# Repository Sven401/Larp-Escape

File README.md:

# Larp-Escape

ESP32-Steuerung des Reichstag-Spiels: Rollenkarten, Kristallmatrix, Audio, LEDs und ESP-NOW-Aktivierung.

**Entwicklungseinstieg · 20.10.2026:** Kanonische Basis ist
`plan/projektuebergabe-kuratierter-stand`, hier gegen `97a2584` geprüft.
Der [Maintainer-Stand](handoff/MAINTAINER.md) führt nächste Arbeit und Grenzen;
[Setup und Prüfwege](handoff/PROJEKT-SETUP.md) erklären die Arbeitsumgebung.
Die [technische Übergabe](handoff/README.md) erschließt datierte Belege und Archive.

| Arbeitsbereich | Vorhandene Grundlage | Einstieg und offene Fortsetzung |
| --- | --- | --- |
| **Larp Dev** · `companion/android/app/` | Baugruppenbedienung und Tests für LED, Wake, Matrix, Audio, NFC und ESP-NOW | [Android-Anleitung](companion/android/README.md); berührte Funktionen am passenden V2-Paar gezielt nachprüfen |
| **Larp GM** · `companion/android/gamemaster/` | Eigenständige App: Station vorbereiten, auswählen, automatisch anmelden und bestätigten Zustand lesen | [Stationspilot](docs/companion/spielleiter-stationspilot.md); Licht-/Spielaktionen und allgemeine Spielleitungsrechte bleiben offen |
| **Baugruppenfirmware** · `firmware/led/` | Gemeinsamer BLE-V2-Vertrag und getrennte Produkt-/Prüfvarianten; eigenständige Kamera-/Effektlabore | [Firmware-Anleitung](firmware/led/README.md), [Wire V2](docs/led/ble-wire-v2.md); gemeinsame Geräteabnahme und Spielanschluss bleiben offen |
| **Spiel- und Profilkern** · `src/`, `include/`, `lib/` | Bestehendes festes Spiel sowie konfigurierbarer Profilkern mit synthetischen Runtime-Proben | [Geräteausführung](docs/configuration/device-runtime.md), [Profilanwendung](docs/configuration/profile-application.md); reale profilabhängige Gerätebesitzer und Produktionsanschluss bleiben offen |

Die Produktquellen sind seit Stationspilot-Merge `7e19c95` unverändert;
die [Wartungsprüfung vom 20.10.2026](handoff/WARTUNG-PRUEFSTAND-2026-10-20.md)
belegt lokale Tests und Builds dieses Standes. Die historischen
[Baugruppenergebnisse](handoff/BAUGRUPPEN-NACHWEISE.md) und der begrenzte
GM-Gerätelauf bleiben erhalten; sie sind keine gemeinsame Gesamtspielabnahme.

**Verbindliches Zielbild:** [Dezentrale Veranstaltung (VA-01)](docs/veranstaltungsarchitektur.md)
mit autonomen Boxen, BLE je Station und unterbrechbarer Infrastruktur.
[D0 und Folgepakete](docs/veranstaltungsarchitektur-umsetzung.md) trennen die
integrierte Spezifikation von ihrer offenen Umsetzung. Für LED-Arbeit gelten
die [Projektgrenzen](docs/led/implementation-reference.md); Näheglut hat einen
[Laborstand und offenen Produktanschluss](docs/led/naeheglut-spielanschluss.md).

## Entwicklung ohne Hardware

PlatformIO Core **6.2.0**, Python **3.11** für B0; der vollständige Python-/Kameratestlauf benötigt **3.12**. Plattformen und Bibliotheken sind in `platformio.ini` festgelegt. Der Host verwendet Windows und C++11. Ein ESP32 wird für diese Schritte nicht benötigt:

```powershell
python scripts/check_architecture.py --self-test
python scripts/check_architecture.py
pio test -e host-regression
pio run -e az-delivery-devkit-v4 -e esp32-runtime-probe
python scripts/check_headers.py
python -m pip install clang-format==19.1.7
python scripts/check_format.py
```

Der [vollständige Prüfweg](docs/quality-checks.md) umfasst zusätzlich konfigurierte
Steuerung, echte Kryptografie, die GATTS-ABI-Probe und Android. Die CI prüft bei
Pull Requests den Zusammenführungsstand mit dem Zielbranch und bewahrt
commitbezogene Prüfprotokolle auch bei Fehlern. Hosttests und Firmware-Build
sind getrennte Nachweise; sie bestätigen weder Verdrahtung noch Timing am Gerät.

## Module

| Schicht | Ort | Aufgabe |
| --- | --- | --- |
| Domain | `include/GameDomain`, `src/GameDomain` | Rollen, Kristalle, Fortschritt und Resetregeln |
| Konfiguration | `include/GameConfiguration`, `src/GameConfiguration` | Begrenzte Profile, semantische Prüfung, JSON-Import/-Export |
| Ausführung | `include/GameExecution`, `src/GameExecution` | Konfigurierbarer Graph und profilabhängige Spielsitzung |
| Geräteplanung | `include/DeviceRuntime`, `src/DeviceRuntime` | Komponentenbesitz, korrelierte kopierte Aufträge und Antworten |
| Ports | `include/GamePorts` | Wertbasierte Schnittstellen für Geräte und Diagnose |
| Anwendung | `lib/GameState`, `lib/GameApplication` | Spielfluss und Reihenfolge der Dienste |
| Zustandsmaschine | `lib/Machine` | Zustandsbesitz, Guards, einmalige Eintrittsaktionen |
| Zeit-/Indexregeln | `include/GameRuntime` | Hostprüfbare Gerätepolitik ohne Treiber |
| Companion-Protokoll | `include/Companion`, `src/Companion` | Begrenzte Statusserialisierung ohne Netzwerkabhängigkeit |
| Adapter | übrige `lib`-Module | Arduino, FreeRTOS und konkrete Geräte |
| Einstieg | `src/main.cpp` | Aufbau, Start und Laufzeitdiagnose |

Die Spiellogik braucht weder Arduino noch Hardware-Stubs. Die alte Regression prüft zusätzlich die konkrete Farbpalettenzuordnung mit kleinen FastLED-Wertstubs; das ist ein Adaptervertrag.

## Laufzeit und Companion

- [ESP32 am USB ohne Zusatzhardware](docs/usb-probe.md)
- [NFC-Paketvertrag und gepinnte Bibliothekskorrektur](docs/nfc-packet-contract.md)
- [Komponentenplanung und FreeRTOS-Auftragskanal](docs/configuration/device-runtime.md)
- [Kontrollierte Profilübernahme und geänderte Einrichtung](docs/configuration/activation.md)
- [Aktives Profil und geschützter Entwurf](docs/configuration/profile-slots.md)
- [Dauerhafte Profile und Wiederanlauf](docs/configuration/profile-journal.md)
- [Gemeinsamer Einrichtungs-/Speicherablauf](docs/configuration/profile-application.md)
- [Profilabhängige Spielsitzung](docs/configuration/session.md)
- [Besitz, Tasks und Grenzen](docs/runtime.md)
- [Companion-Status v1](docs/companion/status-v1.md)
- [Statusschema](docs/companion/status-v1.schema.json)

Unter `companion/android/` liegen die getrennten Kotlin-/Compose-Apps Larp Dev
und Larp GM mit gemeinsamem `core:protocol`. [Apptrennung und Datenerhalt](docs/companion/android-app-trennung.md)
sowie der [lesende GM-Stationspilot](docs/companion/spielleiter-stationspilot.md)
sind implementiert. Allgemeiner Spielzugang, Spielsteuerung und veranstaltungsweite
Verteilung bleiben offen; der Baugruppen-HMAC-Zugang ersetzt keine GM-Rollen.

Die technische Übergabe in `handoff/` ist ohne Zugriff auf frühere interne
Projektwerkzeuge lesbar. Sie nennt die erhaltenen Commitstände, Prüfungen und
offenen Arbeiten.

## Qualitätsumfang

`check_architecture.py` prüft direkte Includes und Schichtrichtungen, nicht den vollständigen C++-Abhängigkeitsgraphen. Makro-Includes und unbekannte Projektincludes scheitern sichtbar. `--self-test` führt sieben isolierte Fixtures aus.

`check_headers.py` übersetzt jeden öffentlichen Header der reinen Schichten separat mit C++11, `-Wall -Wextra -Wpedantic -Werror`, ohne Hardware-Stubs. Der Hostcompiler wird nach den Hosttests von PlatformIO bereitgestellt.

`check_format.py` verwendet exakt clang-format **19.1.7** und `.clang-format`. Die explizite Baseline umfasst die reinen Schichten, die im Skript genannten überarbeiteten Adapter, beide Einstiegspunkte und die neuen Host-Suites. Alte Konfiguration, ArduinoClock, EspNowCommunicator und die frühere `test_regression` bleiben außerhalb der Formatbaseline. `--list` zeigt die konkreten Dateien, `--fix` formatiert ausschließlich diese geprüfte Liste. Den aktuellen Dateiumfang liefert `--list`; neue reine Schichten und der Profilkanal sind einbezogen.

Die Windows-CI ersetzt keine zusätzliche Prüfung von Include-Groß-/Kleinschreibung auf einem case-sensitiven System. Statische Analyse wurde lokal mit Cppcheck 2.1 für die reinen Implementierungen (`warning,performance,portability`) durchgeführt; clang-tidy und eine verpflichtende vollständige Analyse sind noch offen.

## Konfigurierbare Firmware und Companion

Der erste hardwarefreie Profilkern enthält Hardware, Rollen, Zustände, Übergangsbedingungen, Aktionen und Effekte. [Modell, Export und Grenzen](docs/configuration/profile-model.md), [Standardprofil](docs/configuration/standard-profile.json) und [strukturelles JSON-Schema](docs/configuration/profile-v1.schema.json). JSON-Import, Graphauswertung und eine profilabhängige Spielsitzung mit Rechnerbedienung sind implementiert. Komponentenplanung, Broker, statische FreeRTOS-Queues und kontrollierte Profilübernahme mit zwei privaten Profilspeichern sind implementiert und separat mit synthetischen Besitzern baubar. Zwei-Datensatz-Journal und synchronisierter Rechner-Dateispeicher sind implementiert; der ESP32-Speicheradapter ist an die separat gebaute FreeRTOS-Probe angeschlossen. Der gemeinsame Anwendungsablauf koordiniert Einrichtung, Speicherbestätigung und Spielleiterfreigabe in Rechnerwerkzeug und Probe. Für diesen Profilpfad bleiben reale profilabhängige Treiber, Produktionsanschluss, Geräte-/Stromausfallabnahme und die Anbindung an die Android-Apps offen.

Konfigurierbare Graphausführung und Rechner-Vorschau: [Laufzeitvertrag](docs/configuration/execution.md).

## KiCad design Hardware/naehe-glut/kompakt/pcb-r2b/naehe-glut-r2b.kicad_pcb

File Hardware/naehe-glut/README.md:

# Nähe Glut R1: Platine, Gehäuse und Beschaffung

**Historischer R1-Stand, keine aktuelle Bestellbasis:** Der Nutzer verlangt
seit31.10.2026 kleinsten Gesamtformfaktor, ESP-Boards höchstens25×20mm,
vier Stunden Akkulaufzeit als Auslegungsziel und vollständig bestückte Platinen.
Die [Kompaktplanung](kompakt/PLANUNG.md) ersetzt die bisherige Größen-/Teilewahl.
R1 bleibt für Bestellung und Fertigung gesperrt. Eine spätere Autorisierung
der neuen Kompaktvariante hebt diesen R1-Bestellstopp nicht auf.

Stand: **31. Oktober 2026**. Prototyprevision für zwei ESP32-S3-Stationen.
Digitale Fertigungsunterlagen sind erstellt; der abschließende Freigabestand
und konkrete Prüfgrenzen stehen im [unabhängigen Review](REVIEW.md).
Es wurde noch nichts bestellt, gedruckt, bestückt oder auf Geräte geladen.

## Benutzen

- [PCB-Fertigungspaket als ZIP](pcb/exports/naehe-glut-r1-fertigung.zip)
  und [Druckpaket als ZIP](fertigung/NG-R1-Druckpaket.zip).
- [Bestellliste für beide Geräte](BESTELLUNG.md): Boards, Ringe, Akkus,
  Drucker, Filament, Kabel und Montagebedarf.
- [PCB-Bauteile](pcb/BOM.md) und [Fertigung/elektrische Montage](pcb/FERTIGUNG.md).
- [Gehäusemontage](mechanik/MONTAGE.md) und [Druckprojekte/Prüfweg](mechanik/DRUCK.md).
- Native KiCad-Dateien unter `pcb/`; FCStd, STEP und STL unter `mechanik/`;
  sechs vorbereitete A1-mini-Projekte unter `mechanik/print/`.

## Festgelegter Aufbau

ESP32-S3-DevKitC-1-N16R8 von Espressif, Adafruit-1586-Ring mit **24 Pixeln**,
Voltaic-V50-Akku und zweilagige Carrierplatine, 85×80 mm. GPIO15 führt
LED-Daten, GPIO16 gibt die 5-V-Pufferstufe frei. Der Carrier versorgt keine
ESP-5V-/3V3-Pins; zwei USB-A-Kabel vom Akku speisen getrennte Pluspfade bei
gewollt gemeinsamer Masse. Laden erfolgt mit entnommenem Akku.

Beschaffungsänderung vom 31.10.2026 auf Basis `e9e2afe`: Das lieferbare
Original-N16R8 ersetzt N8R8 mit denselben Carrieranschlüssen. Der Schaltplan
behält die ursprüngliche N8R8-Bezeichnung; mechanische und elektrische
Carrierdateien bleiben unverändert. Die Firmware braucht 16 MB Quad-Flash
und weiterhin 8 MB Octal-PSRAM; eine Geräteprüfung steht aus.

Das PETG-Gehäuse misst 168×148×90 mm ohne Schraubenköpfe. Boden, Träger,
Deckel, Ringhalter und Diffusor sind getrennt druckbar; ein Coupon prüft
vorab Schrauben-/Mutternpassung. Drucker: Bambu Lab A1 mini, 0,4-mm-Düse,
ohne AMS. Vier Nylonbefestiger halten die PCB im Antennenbereich. Schwarze
Teile verwenden nun **Bambu PETG Basic 30105**, der Diffusor weiter PETG
Translucent Clear. Alle sechs Druckprojekte sind neu berechnet; etwa 11,7 Stunden
Maschinenzeit je Station. Beschaffungsquellen und Trocknung stehen in der Bestellliste.

Die Auslegung gilt für trockenen, vor Regen geschützten Einsatz. Eine konkrete
Mindestlaufzeit wurde nicht vorgegeben; die Bestellliste enthält gekennzeichnete
Laufzeitrechnungen. Keine IP-, Wärme- oder Funkfreigabe wird aus CAD/Slicer
abgeleitet. Ein ausgeschalteter ESP löscht gespeicherte Pixelfarben nicht;
für Service beide Versorgungszweige trennen.

## Auftrag, Zuständigkeit und Termin

Quelle: Nutzerauftrag in Codex-Sitzung `01a192e5-6a3d-7ce2-a9e1-bfacd9a97e3b`,
31.10.2026, Basiscommit `63477d08e160d1b1f81b37bbd16593c1a2087624`:
bestellbare PCB und druckbares Gehäuse; Komponentenwahl, Akkukonzept und
Druckerauswahl ausdrücklich delegiert.

Koordination/Maintainer und Beschaffung: `/root`; Elektronik:
`/root/hardware_developer`; Mechanik: `/root/enclosure_developer`;
unabhängige Gegenprüfung Gerätevertrag/Qualität: `/root/hardware_review`.
Beschaffungsnachtrag: `/root` verantwortlich, `/root/filament_supply` setzt
Materialprofile um, `/root/supply_review` prüft unabhängig gegen.
Eigene Umsetzung gilt nicht als unabhängiger Review.

**Zwei funktionierende Exemplare bis Dezember 2026 bleiben das Lieferziel.**
Eine eigene PCB darf diesen Termin nicht gefährden. Die
[kanonische Hardwareplanung](../HARDWAREPLANUNG.md) behält Vorrang; bei
Fertigungsrisiko ist parallel ein Aufbau mit vorhandenen Boards/Modulen
vorzusehen. Das genaue Dezemberdatum ist weiterhin offen.

Diese Dateien liefern die Hardwareentwicklung. Firmwareportierung auf S3/R1,
schwarzer Startframe mit 24 Pixeln, Effekt/Funk zwischen beiden Geräten,
Probemontage, Last-/Wärmeprüfung und Dauerlauf bleiben gesonderte Arbeit.
Die alte ESP32-Box und ihr 23-Pixel-Aufbau werden durch R1 nicht umgebaut.

## Werkzeuge und Nachweise

| Bereich | Werkzeug / Beleg | Aussage |
| --- | --- | --- |
| Elektronik | KiCad 10.0.8; `pcb/pruefung/` | ERC, DRC, Netzlisten-/Layoutabgleich und CAM-Prüfung gemäß Review |
| Geometrie | FreeCAD 1.0.2; `mechanik/geometry-report.json` | Gültige Körper, STEP-Rückimport, geschlossene STL-Netze, Kollisionen und Bezug auf den echten PCB-STEP |
| Druck | Bambu Studio 2.8.2.61; `mechanik/slice-report.json` | Alle sechs Teile erfolgreich berechnet; Datei-Hashes, Material und Zeitabschätzungen |
| Gegenprüfung | `REVIEW.md` | Unabhängige konkrete Befunde, Freigabeumfang und offene physische Nachweise |

Generatoren liegen unter `tools/`. Montage- und Druckanleitungen nennen die
reproduzierbaren Aufrufe. Lokale Werkzeugdownloads, Probeläufe und Sicherungen
unter `.tmp/` sind keine Lieferdateien. PCB-Änderungen erfordern neuen Export
und Geometrieabgleich; Änderungen an Druckteilen erfordern neue Slicerprojekte.

„Bestellbar“ bedeutet geprüftes Prototyp-Fertigungspaket mit eindeutiger
Stückliste, keine gesicherte Lagerverfügbarkeit und keinen ausgelösten Kauf.
„Druckbar“ bedeutet digital geprüfte Druckdateien, keine bestandene physische
Passprobe oder Produktabnahme.

## Abgrenzung bestehender Vorarbeiten

[Issue #112](https://github.com/Sven401/Larp-Escape/issues/112) und
[PR #113](https://github.com/Sven401/Larp-Escape/pull/113) führen das
Vollboxkonzept PCB-K0. DFPlayer, MCP und weitere Vollboxfunktionen werden
daraus nicht als Bauumfang dieser Nähe-Glut-Variante übernommen.
Historische Schaltplanquellen bleiben im [Quelleninventar](../QUELLENINVENTAR.md).

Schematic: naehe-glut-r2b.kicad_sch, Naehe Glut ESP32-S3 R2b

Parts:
C1, C2: 10uF 10V X5R; C_0805_2012Metric; MPN GRM21BR61A106KE19L
C3, C4, C6, C17, C18: 22uF 16V X6S; C_0805_2012Metric; MPN GRM21BC81C226ME44L
C5, C7, C20: 10uF 25V X5R; C_0603_1608Metric; MPN TMK107BBJ106MA-T
C8, C9, C11, C19: 100nF 16V X7R; C_0402_1005Metric; MPN GRM155R71C104KA88D
C10, C12: 1uF 10V X5R; C_0402_1005Metric; MPN GRM155R61A105KE15D
C13: 22nF 50V X7R; C_0402_1005Metric; MPN GRM155R71H223KA12D
C14: 22uF 10V X5R; C_0805_2012Metric; MPN GRM21BR61A226ME44L
C16: 470uF 6.3V polymer10mOhm; CP_EIA-7343-43_Kemet-X; MPN T530X477M006ATE010
C21: 1uF 10V X5R startup delay; C_0603_1608Metric; MPN GRM188R61A105KA61D
C22: 220pF 50V C0G feedforward; C_0402_1005Metric; MPN GRM1555C1H221JA01D
C23, C24, C25: 100n; C_0603_1608Metric; MPN GRM188R71C104KA01D
C26, C27: 10n; C_0603_1608Metric; MPN GRM188R71H103KA01D
C28: 100n 16V X7R / input not stability-critical; C_0603_1608Metric; MPN GRM188R71C104KA01D
C29, C30: 4.7u 16V X7R / two parallel for bias reserve; C_0805_2012Metric; MPN GRM21BR71C475KE51L
C31: 100n inverter bypass; C_0603_1608Metric; MPN GRM188R71C104KA01D
D1, D2, D3, D4, D5: rail-free ESD array; Texas_DRT-3; MPN TPD2EUSB30DRTR
F1: 2A fast fuse; Fuse_0603_1608Metric; MPN 0467002.NRHF
J1: BAT JST PH2 vertical; JST_PH_B2B-PH-SM4-TB_1x02-1MP_P2.00mm_Vertical; MPN B2B-PH-SM4-TB(LF)(SN)
J2: LED wire pads; LED_3WirePads; MPN PCB integral solder pads
J3: External EG1218 EN switch; Switch_2WirePads; MPN PCB integral solder pads
J4: USB-C DATA ONLY / external target supply; USB_C_Receptacle_GCT_USB4105-xx-A_16P_TopMnt_Horizontal; MPN USB4105-GF-A
J5: GPIO JTAG / VTref reference only; FTSH105_007_K; MPN FTSH-105-01-L-DV-007-K
JP1: OPEN USB / CLOSED GPIO after authorized eFuse; PinHeader_1x02_P2.54mm_Vertical; MPN TSW-102-07-G-S
L1: 1uH; L_Coilcraft_XxL4030; MPN XEL4030-102MEC
L2: 1.5uH; L_Coilcraft_XAL4020-XXX; MPN XFL4020-152MEC
Q1: MMBT3904 NPN OE pull-down; SOT-323_SC-70; MPN MMBT3904WT1G
R1: 33.2k; R_0402_1005Metric; MPN 0402WGF3322TCE
R2, R7: 100k; R_0402_1005Metric; MPN RT0402BRD07100KL
R3: 12.1k; R_0402_1005Metric; MPN RT0402BRD0712K1L
R4, R6: 750k; R_0402_1005Metric; MPN MCS0402MD7503BE000
R5: 22k; R_0402_1005Metric; MPN RC0402FR-0722KL
R8, R9, R10, R11, R24, R26: 10k; R_0402_1005Metric; MPN RC0402FR-0710KL
R12, R14, R16, R19: 100k; R_0402_1005Metric; MPN RC0402FR-07100KL
R13: 100; R_0402_1005Metric; MPN RC0402FR-07100RL
R15: 330; R_0402_1005Metric; MPN RC0402FR-07330RL
R17: 470 ohm 0.1W; R_0603_1608Metric; MPN RC0603FR-07470RL
R18: 680; R_0402_1005Metric; MPN RC0402FR-07680RL
R22: 470k; R_0402_1005Metric; MPN MCS0402MD4703BE000
R23: 150k; R_0402_1005Metric; MPN RT0402BRD07150KL
R25: 6.8k; R_0402_1005Metric; MPN RC0402FR-076K8L
R27: 1k; R_0402_1005Metric; MPN RC0402FR-071KL
R28, R29: 5K1; R_0402_1005Metric; MPN RC0402FR-075K1L
R30, R31: 22R; R_0402_1005Metric; MPN RC0402FR-0722RL
R32, R33, R34, R35, R46: 10K; R_0402_1005Metric; MPN RC0402FR-0710KL
R36, R37, R38, R39: 33R; R_0402_1005Metric; MPN RC0402FR-0733RL
R40: 200K; R_0402_1005Metric; MPN RT0402BRD07200KL
R41: 75K; R_0402_1005Metric; MPN RT0402BRD0775KL
R42, R45: 47K; R_0402_1005Metric; MPN RC0402FR-0747KL
R47: 169K; R_0402_1005Metric; MPN RT0402BRD07169KL
R48: 100K; R_0402_1005Metric; MPN RT0402BRD07100KL
SW1: BOOT; SW_Push_1P1T_NO_CK_KMR2; MPN KMR221NGLFS
SW2: RESET; SW_Push_1P1T_NO_CK_KMR2; MPN KMR221NGLFS
TP1: UART0_TX_GPIO43; TestPad_1mm; MPN PCB integral test pad
TP2: UART0_RX_GPIO44; TestPad_1mm; MPN PCB integral test pad
TP3: ROM_BOOT0; TestPad_1mm; MPN PCB integral test pad
TP4: RESET_EN; TestPad_1mm; MPN PCB integral test pad
TP5: GND; TestPad_1mm; MPN PCB integral test pad
TP6: SENSE_ONLY_NO_POWER_IN; TestPad_1mm; MPN PCB integral test pad
U1: ESP32-S3-MINI-1-N4R2; ESP32-S2-MINI-1; MPN ESP32-S3-MINI-1-N4R2
U2: 5.1V LED boost; SOT-563; MPN TPS61023DRLR
U3: 3V3 independent buck-boost; TI_RNM0015A; MPN TPS63070RNMR
U4: UVLO with hysteresis; SOT-23-6; MPN TPS3700DDCR
U5: LED input current limiter latch-off; SOT-23-6; MPN TPS2553DBVR-1
U6: LED translating data buffer; SOT-353_SC-70-5; MPN SN74LV1T125DCKR
U7: LED load switch; SOT-23-6; MPN TPS22918DBVR
U8: USB hardware disconnect; Texas_UQFN-10_1.5x2mm_P0.5mm; MPN TS3USB221ARSER
U9, U10: USB attach supervisor; TI_DSE0006A; MPN TPS389001DSER
U11: USB interface ONLY / no target power; SOT-23-5; MPN TPS70933DBVR
U12: USB ready Schmitt inverter; SOT-353_SC-70-5; MPN SN74LVC1G14DCKR

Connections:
/+3V3: C6.1, C7.1, C8.1, C17.1, C18.1, D4.2 (IO2), J5.1, R8.1, R9.1, R11.1, R22.1, R32.1, R33.1, R34.1, R47.1, TP6.1, U1.3 (3V3), U3.7 (VOUT), U3.8 (VOUT)
/+5V: C3.1, C4.1, C12.1, C22.1, R6.1, U2.6 (VOUT), U7.1 (VIN)
/BAT_FUSED: C1.1, C5.1, C9.1, C20.1, F1.2, R2.1, R5.1, R26.1, U3.12 (VIN), U3.13 (VIN), U4.5 (VDD), U5.1 (IN)
/BAT_LIMITED: C2.1, L1.1, U2.3 (VIN), U5.6 (OUT)
/BAT_RAW: F1.1, J1.1
/BOOST_FB: C22.2, R6.2, R7.1, U2.1 (FB)
/BOOST_SW: L1.2, U2.5 (SW)
/BOOT0: R9.2, SW1.1, TP3.1, U1.4 (IO0)
/CHIP_EN: D4.1 (IO1), J5.10, R8.2, R25.1, SW2.1, TP4.1, U1.45 (EN), U3.2 (PG)
/FAULT_N: R11.2, U1.15 (IO11), U5.4 (FAULT)
/GND: C1.2, C2.2, C3.2, C4.2, C5.2, C6.2, C7.2, C8.2, C9.2, C10.2, C11.2, C12.2, C13.2, C14.2, C16.2, C17.2, C18.2, C19.2, C20.2, C21.2, C23.2, C24.2, C25.2, C26.2, C27.2, C28.2, C29.2, C30.2, C31.2, D1.3 (GND), D2.3 (GND), D3.3 (GND), D4.3 (GND), D5.3 (GND), J1.2, J2.2, J3.2, J4.A1, J4.A12, J4.B1, J4.B12, J4.SH, J5.3, J5.5, JP1.2, Q1.2 (E), R1.2, R3.2, R7.2, R10.2, R12.2, R14.2, R16.2, R19.2, R23.2, R28.2, R29.2, R35.2, R41.2, R46.2, R48.2, SW1.2, SW2.2, TP5.1, U1.1 (GND), U1.2 (GND), U1.42 (GND), U1.43 (GND), U1.46 (GND), U1.47 (GND), U1.48 (GND), U1.49 (GND), U1.50 (GND), U1.51 (GND), U1.52 (GND), U1.53 (GND), U1.54 (GND), U1.55 (GND), U1.56 (GND), U1.57 (GND), U1.58 (GND), U1.59 (GND), U1.60 (GND), U1.61 (GND), U1.62 (GND), U1.63 (GND), U1.64 (GND), U1.65 (GND), U2.4 (GND), U3.4 (GND), U3.10 (PGND), U3.15 (VSEL), U4.2 (GND), U4.4 (INB-), U5.2 (GND), U6.3 (GND), U7.2 (GND), U8.5 (GND), U8.9 (S), U9.2 (GND), U10.2 (GND), U11.2 (GND), U12.3 (GND)
/GPIO8_DATA: R13.1, U1.12 (IO8)
/GPIO9_OE: R18.1, U1.13 (IO9)
/GPIO10_LED_EN: R12.1, U1.14 (IO10), U2.2 (EN), U5.3 (EN), U7.3 (ON)
/GPIO46_STRAP: R10.1, U1.44 (IO46)
/ILIM: R1.1, U5.5 (ILIM)
/JTAG_SEL: JP1.1, R32.2, U1.7 (IO3)
/JTAG_TCK: R35.1, R36.2, U1.35 (IO39)
/JTAG_TCK_PORT: D2.2 (IO2), J5.4, R36.1
/JTAG_TDI: R34.2, R38.2, U1.37 (IO41)
/JTAG_TDI_PORT: D3.2 (IO2), J5.8, R38.1
/JTAG_TDO: R39.1, U1.36 (IO40)
/JTAG_TDO_PORT: D3.1 (IO1), J5.6, R39.2
/JTAG_TMS: R33.2, R37.2, U1.38 (IO42)
/JTAG_TMS_PORT: D2.1 (IO1), J5.2, R37.1
/LED5V: C11.1, C14.1, C16.1, J2.1, R17.1, R27.1, U6.5 (VCC), U7.6 (VOUT)
/LED_A: R13.2, R14.1, U6.2 (A)
/LED_CT: C13.1, U7.4 (CT)
/LED_DATA: J2.3, R15.2, R16.1
/LED_OE_N: Q1.3 (C), R17.2, U6.1 (OE_N)
/LED_QOD: R27.2, U7.5 (QOD)
/LED_Y: R15.1, U6.4 (Y)
/MCU_FB: R22.2, R23.1, U3.5 (FB)
/MCU_L1: L2.1, U3.11 (L1)
/MCU_L2: L2.2, U3.9 (L2)
/MCU_PS: R26.2, U3.1 (PS_SYNC)
/MCU_REG_EN: C21.1, R24.2, U3.14 (EN)
/MCU_VAUX: C19.1, U3.3 (VAUX)
/OE_GATE: Q1.1 (B), R18.2, R19.1
/RC_EN: C10.1, R25.2
/SYS_EN: J3.1, R4.1, R5.2, R24.1, U4.1 (OUTA)
/UART_RX: TP2.1, U1.40 (RXD0)
/UART_TX: TP1.1, U1.39 (TXD0)
/USB_CC1: D5.1 (IO1), J4.A5, R28.1
/USB_CC2: D5.2 (IO2), J4.B5, R29.1
/USB_DM_HOST: D1.2 (IO2), J4.A7, J4.B7, U8.7 (D-)
/USB_DM_ISO: R30.2, U8.2 (1D-)
/USB_DM_MCU: R30.1, U1.23 (USB_D-)
/USB_DP_HOST: D1.1 (IO1), J4.A6, J4.B6, U8.8 (D+)
/USB_DP_ISO: R31.2, U8.1 (1D+)
/USB_DP_MCU: R31.1, U1.24 (USB_D+)
/USB_IF_3V3: C23.1, C24.1, C25.1, C29.1, C30.1, C31.1, R42.1, R45.1, R46.1, U8.10 (VCC), U9.3 (MR_N), U9.4 (VDD), U10.3 (MR_N), U10.4 (VDD), U11.5 (OUT), U12.5 (VCC)
/USB_OE_N: R45.2, U8.6 (OE_N), U12.4 (Y)
/USB_READY: R42.2, U9.6 (RESET_N), U10.6 (RESET_N), U12.2 (A)
/USB_TARGET_CT: C26.1, U9.5 (CT)
/USB_TARGET_SENSE: R47.2, R48.1, U9.1 (SENSE)
/USB_VBUS: C28.1, J4.A4, J4.A9, J4.B4, J4.B9, R40.1, U11.1 (IN)
/USB_VBUS_CT: C27.1, U10.5 (CT)
/USB_VBUS_SENSE: R40.2, R41.1, U10.1 (SENSE)
/UV_SENSE: R2.2, R3.1, R4.2, U4.3 (INA+)

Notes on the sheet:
NAEHE GLUT R2b | ELECTRICAL DRAFT - NOT RELEASED FOR MANUFACTURING
Independent MCU buck-boost; current-limited LED boost; UVLO; USB data service, external target supply; no charger.
Battery pack/charger qualification and PWM transient survival remain mandatory order gates.

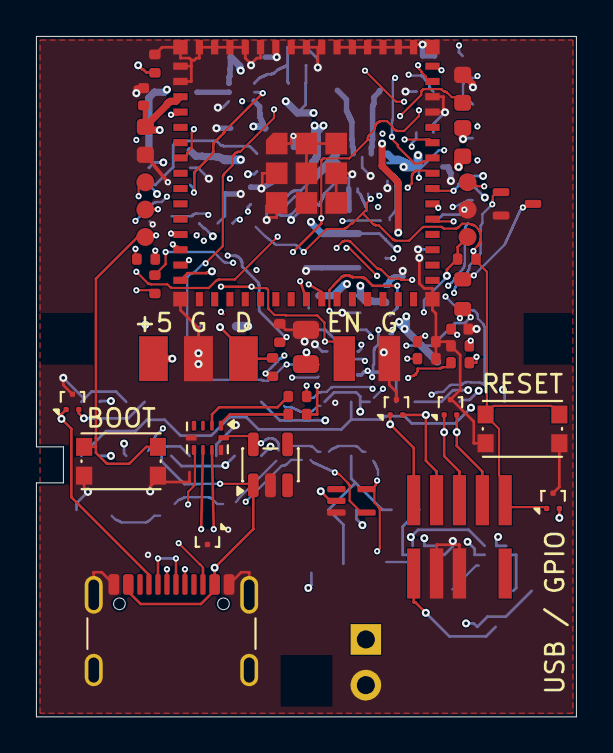
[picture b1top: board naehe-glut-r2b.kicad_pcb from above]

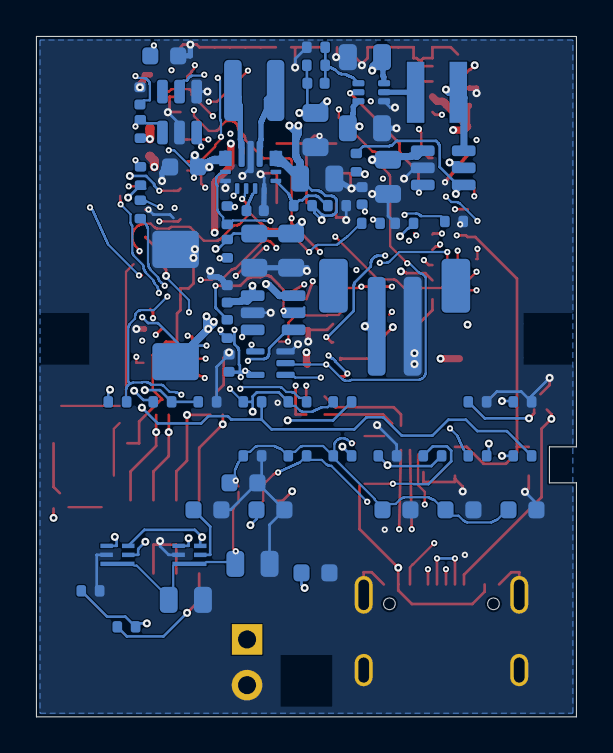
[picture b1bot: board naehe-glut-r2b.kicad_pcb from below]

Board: 6 copper layers, 30.0 x 37.8 mm, 109 parts (67 on the bottom side), 60 nets.

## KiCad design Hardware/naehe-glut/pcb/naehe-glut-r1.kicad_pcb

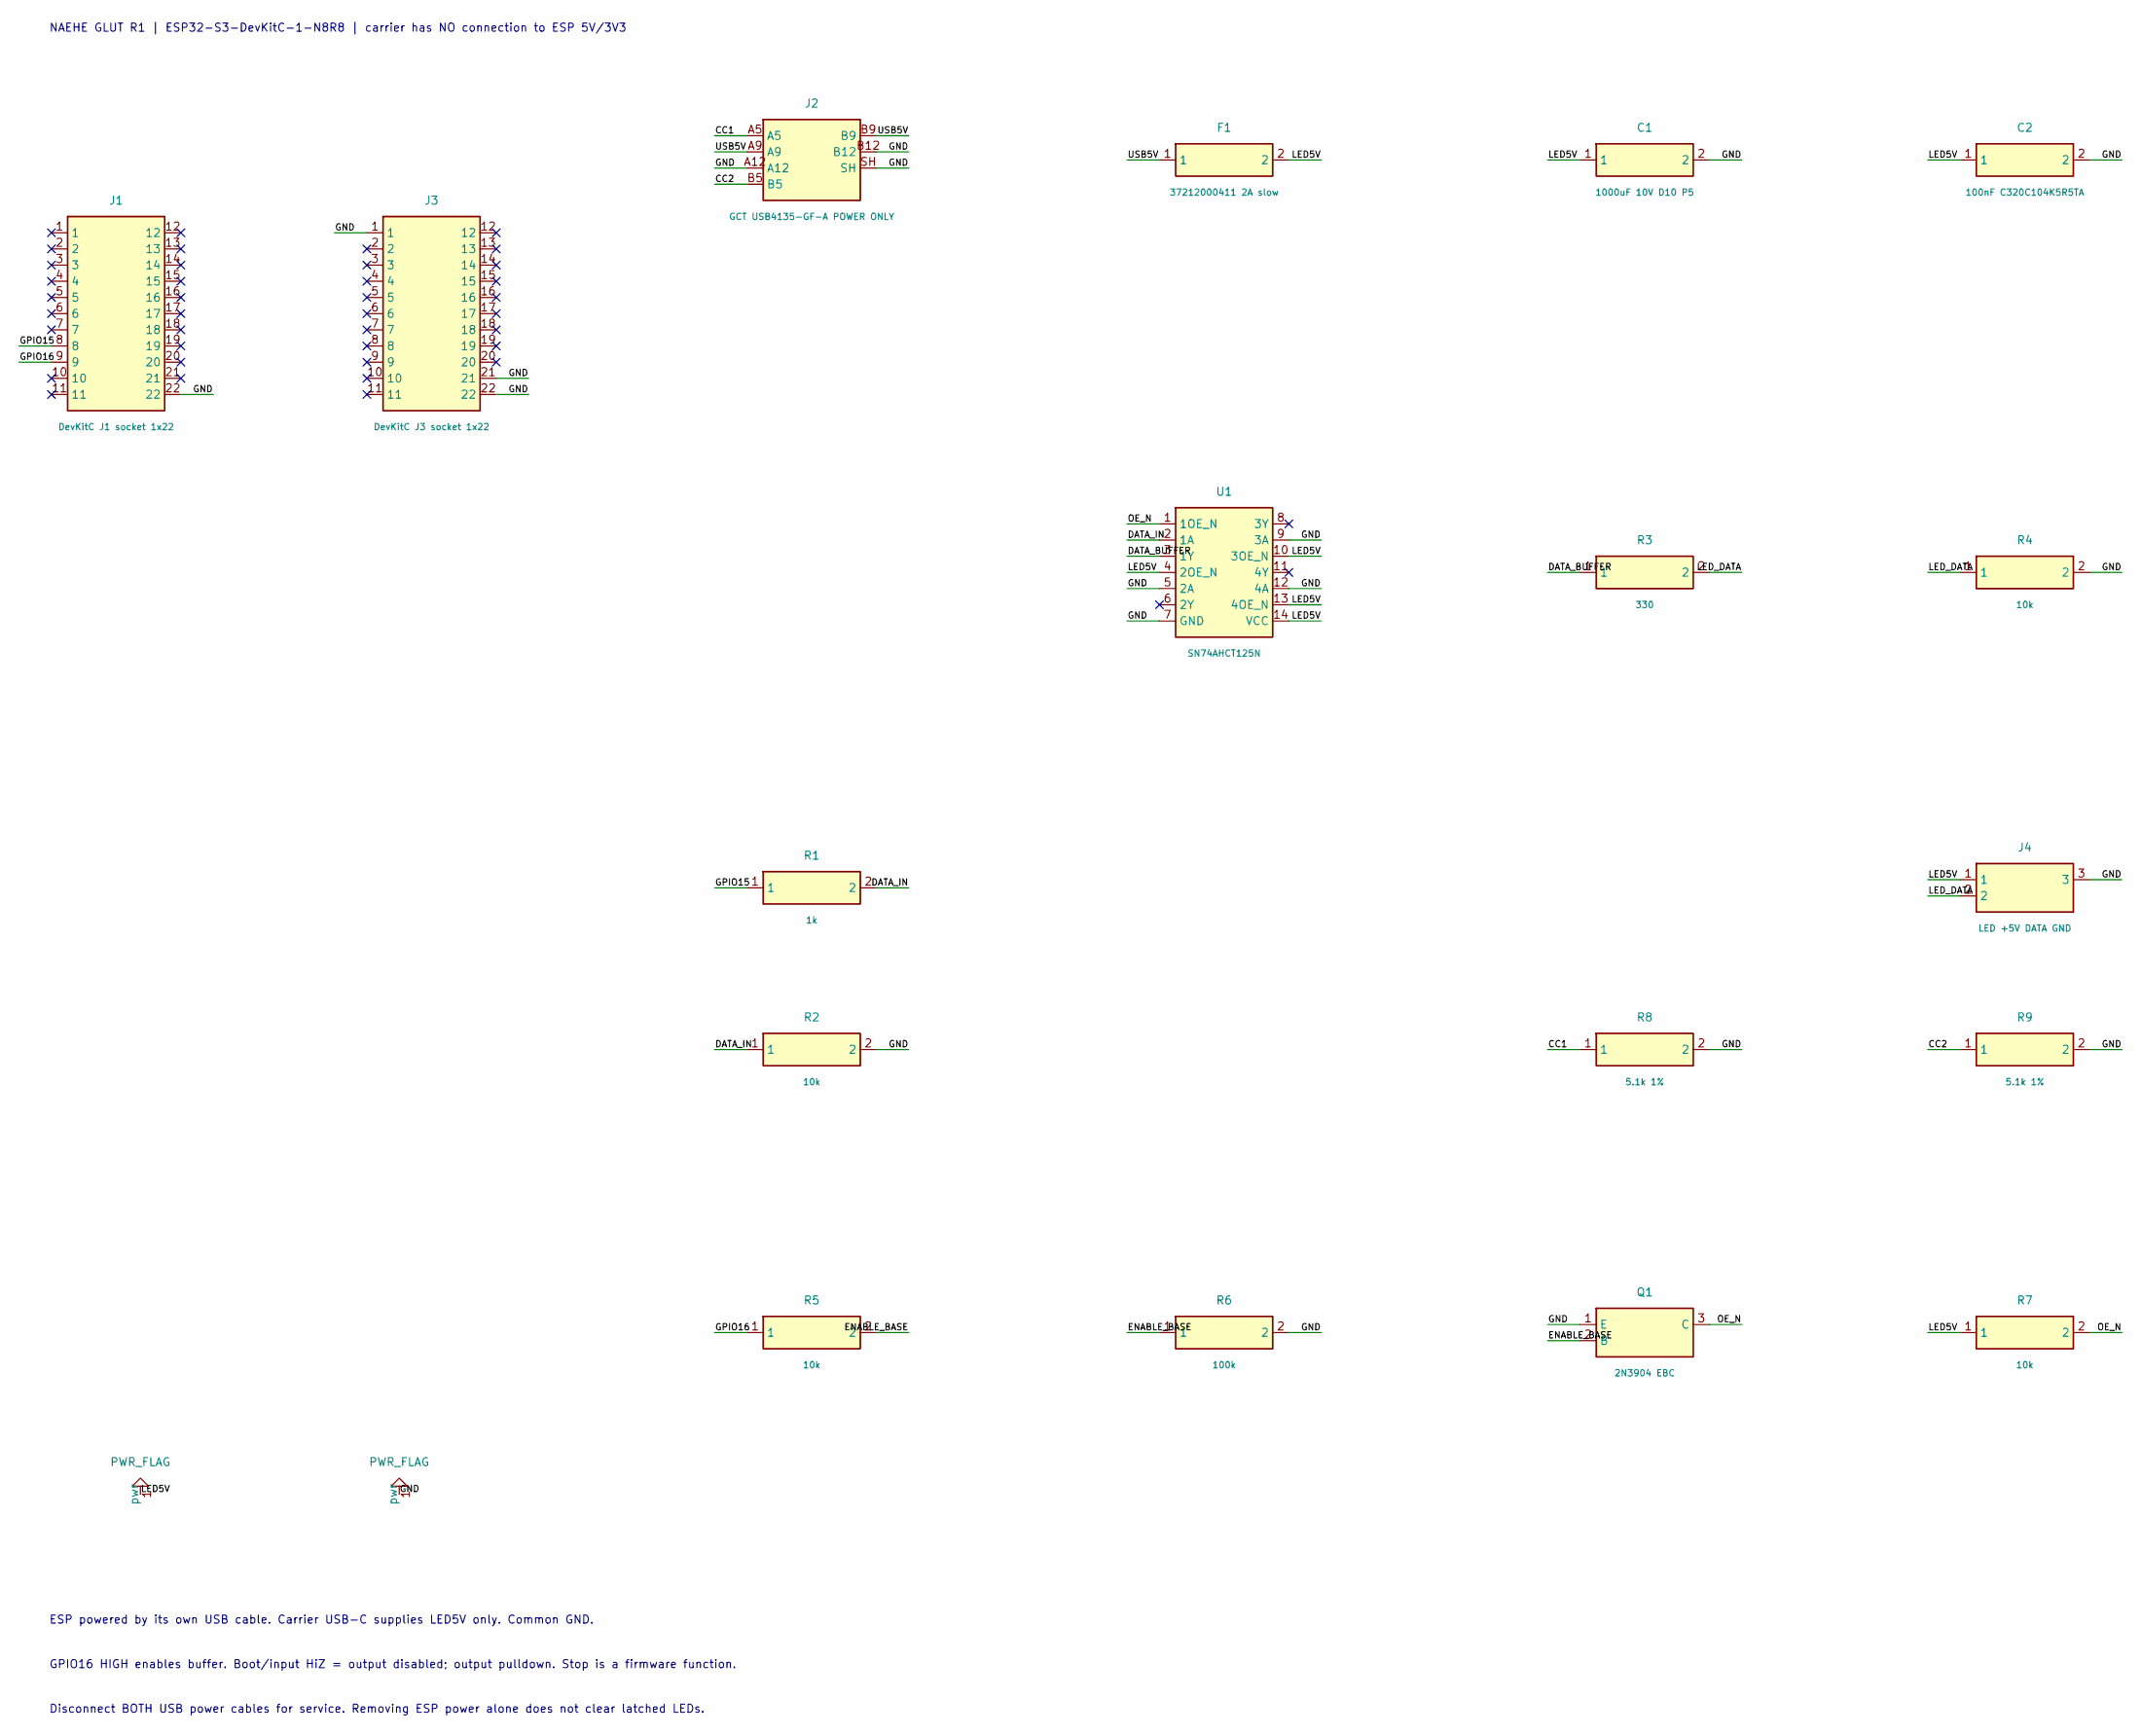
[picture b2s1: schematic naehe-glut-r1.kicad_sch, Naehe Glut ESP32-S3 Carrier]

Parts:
C1: 1000uF 10V D10 P5; CP_Radial_D10.0mm_P5.00mm
C2: 100nF C320C104K5R5TA; C_Kemet_C320_P2.54mm
F1: 37212000411 2A slow; Fuse_Littelfuse_372_D8.50mm
J1: DevKitC J1 socket 1x22; PinSocket_1x22_P2.54mm_Vertical
J2: GCT USB4135-GF-A POWER ONLY; USB_C_Receptacle_GCT_USB4135-GF-A_6P_TopMnt_Horizontal
J3: DevKitC J3 socket 1x22; PinSocket_1x22_P2.54mm_Vertical
J4: LED +5V DATA GND; TerminalBlock_Phoenix_MKDS-1,5-3-5.08_1x03_P5.08mm_Horizont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
Q1: 2N3904 EBC; TO-92_Inline_Wide
R1: 1k; R_Axial_DIN0207_L6.3mm_D2.5mm_P10.16mm_Horizontal
R2, R4, R5, R7: 10k; R_Axial_DIN0207_L6.3mm_D2.5mm_P10.16mm_Horizontal
R3: 330; R_Axial_DIN0207_L6.3mm_D2.5mm_P10.16mm_Horizontal
R6: 100k; R_Axial_DIN0207_L6.3mm_D2.5mm_P10.16mm_Horizontal
R8, R9: 5.1k 1%; R_Axial_DIN0207_L6.3mm_D2.5mm_P10.16mm_Horizontal
U1: SN74AHCT125N; DIP-14_W7.62mm

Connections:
/CC1: J2.A5, R8.1
/CC2: J2.B5, R9.1
/DATA_BUFFER: R3.1, U1.3 (1Y)
/DATA_IN: R1.2, R2.1, U1.2 (1A)
/ENABLE_BASE: Q1.2 (B), R5.2, R6.1
/GND: C1.2, C2.2, J1.22, J2.A12, J2.B12, J2.SH, J3.1, J3.21, J3.22, J4.3, Q1.1 (E), R2.2, R4.2, R6.2, R8.2, R9.2, U1.5 (2A), U1.7 (GND), U1.9 (3A), U1.12 (4A)
/GPIO15: J1.8, R1.1
/GPIO16: J1.9, R5.1
/LED5V: C1.1, C2.1, F1.2, J4.1, R7.1, U1.4 (2OE_N), U1.10 (3OE_N), U1.13 (4OE_N), U1.14 (VCC)
/LED_DATA: J4.2, R3.2, R4.1
/OE_N: Q1.3 (C), R7.2, U1.1 (1OE_N)
/USB5V: F1.1, J2.A9, J2.B9

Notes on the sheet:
NAEHE GLUT R1 | ESP32-S3-DevKitC-1-N8R8 | carrier has NO connection to ESP 5V/3V3
ESP powered by its own USB cable. Carrier USB-C supplies LED5V only. Common GND.
GPIO16 HIGH enables buffer. Boot/input HiZ = output disabled; output pulldown. Stop is a firmware function.
Disconnect BOTH USB power cables for service. Removing ESP power alone does not clear latched LEDs.

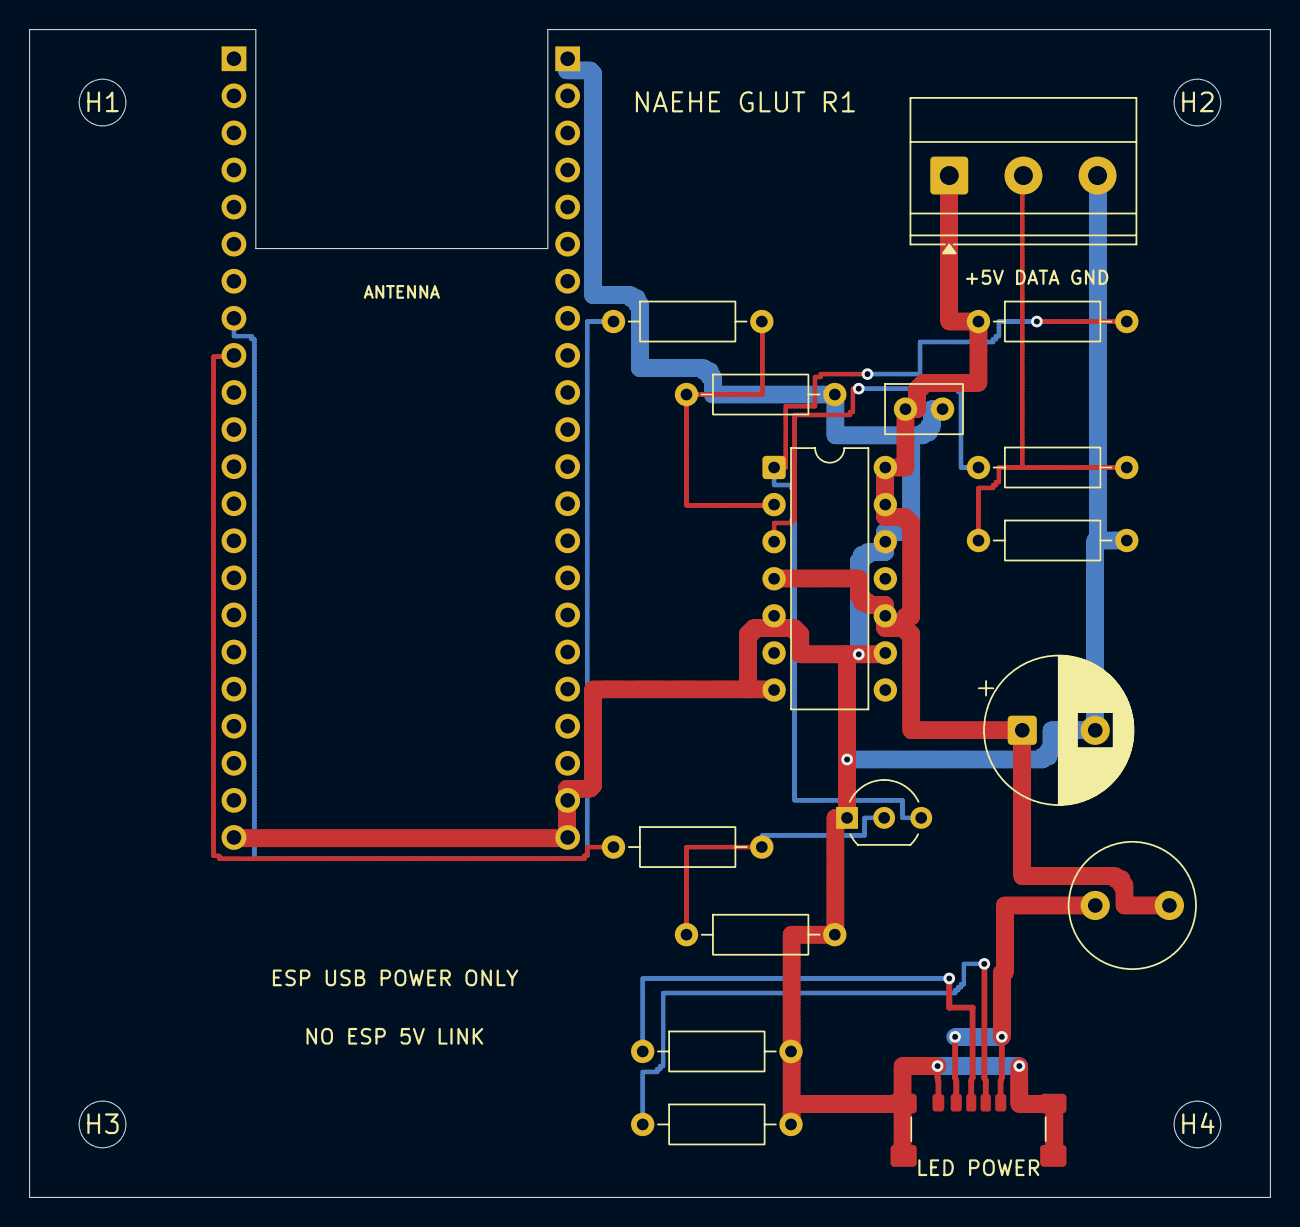
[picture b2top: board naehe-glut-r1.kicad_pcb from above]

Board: 2 copper layers, 85.0 x 80.0 mm, 22 parts (0 on the bottom side), 12 nets.

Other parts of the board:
H1, H2, H3, H4: M3 NPTH

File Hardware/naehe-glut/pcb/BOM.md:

# R1: Bestückungsliste für zwei Carrier

Stand 31.10.2026. Diese Liste gehört ausschließlich zur R1-Schaltung in
`circuit.json`. Die Mengen enthalten keine bereits vorhandenen Teile.
Bestand und Liefertermin beim Bestellen prüfen; ein Link ist kein reservierter
Lagerbestand. Hauptmodule, Akkus, Kabel und Drucker stehen in der übergeordneten
Beschaffungsliste. Nicht allein anhand ähnlich klingender Ersatztypen bestellen.

| Ref. | Hersteller / exakte Bestellnummer | Je PCB | Für zwei | Empfohlener Einkauf inkl. Reserve | Quelle / Bestellung |
| --- | --- | ---: | ---: | ---: | --- |
| J1, J3 | Samtec SSW-122-01-G-S, Buchsenleiste 1×22, 2.54 mm | 2 | 4 | 6 | [Samtec](https://www.samtec.com/products/ssw-122-01-g-s) |
| J2 | GCT USB4135-GF-A, USB-C 6 Kontakte, power-only, 3 A | 1 | 2 | 3 | [GCT mit Distributorbestand](https://gct.co/connector/usb4135) |
| J4 | Phoenix Contact 1715734, MKDS 1,5/3-5,08 | 1 | 2 | 3 | [Hersteller](https://www.phoenixcontact.com/en-us/products/printed-circui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 |
| U1 | Texas Instruments SN74AHCT125N, PDIP-14 | 1 | 2 | 3 | [TI](https://www.ti.com/product/SN74AHCT125/part-details/SN74AHCT125N) |
| Q1 | onsemi 2N3904BU, TO-92, 1=E / 2=B / 3=C | 1 | 2 | 5 | [Herstellerdatenblatt](https://www.onsemi.com/pdf/datasheet/2n3904-d.pdf), [Artikelsuche](https://www.mouser.de/c/?q=2N3904BU) |
| F1 | Littelfuse 37212000411, TR5, 2 A träge, Raster 5.08 mm | 1 | 2 | 5 | [Herstellerdatenblatt](https://www.littelfuse.com/assetdocs/littelfuse_fuse_372_dat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, [Artikelsuche](https://www.mouser.de/c/?q=37212000411) |
| C1 | Panasonic EEUFR1A102, 1000 µF / 10 V, Ø10 × 16 mm, Raster 5 mm | 1 | 2 | 3 | [Panasonic mit Bestandssuche](https://industrial.panasonic.com/ww/products/pt/aluminum-cap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 |
| C2 | KEMET C320C104K5R5TA, 100 nF / 50 V, X7R, 10 %, Raster 2.54 mm | 1 | 2 | 5 | [Herstellermaßblatt](https://yageogroup.com/component-documentation/download/spec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, [DigiKey](https://www.digikey.de/en/products/detail/kemet/C320C104K5R5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 |
| R1 | Yageo MFR-25FBF52-1K, 1 kΩ, 1 %, 0.25 W | 1 | 2 | 10 | [Artikelsuche](https://www.mouser.de/c/?q=MFR-25FBF52-1K) |
| R2, R4, R5, R7 | Yageo MFR-25FBF52-10K, 10 kΩ, 1 %, 0.25 W | 4 | 8 | 20 | [Artikelsuche](https://www.mouser.de/c/?q=MFR-25FBF52-10K) |
| R3 | Yageo MFR-25FBF52-330R, 330 Ω, 1 %, 0.25 W | 1 | 2 | 10 | [Artikelsuche](https://www.mouser.de/c/?q=MFR-25FBF52-330R) |
| R6 | Yageo MFR-25FBF52-100K, 100 kΩ, 1 %, 0.25 W | 1 | 2 | 10 | [Artikelsuche](https://www.mouser.de/c/?q=MFR-25FBF52-100K) |
| R8, R9 | Yageo MFR-25FBF52-5K1, 5.1 kΩ, 1 %, 0.25 W | 2 | 4 | 10 | [Artikelsuche](https://www.mouser.de/c/?q=MFR-25FBF52-5K1) |

Die Widerstände haben nach [Yageo MFR-Datenblatt](https://yageogroup.com/content/datasheet/asset/file/YAGEO-MF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
6.3 ± 0.5 mm Körperlänge und 2.4 ± 0.2 mm Durchmesser. Auf 10.16 mm Raster
formen, ohne Zug direkt am Bauteilkörper. Q1-Beine für den vorgesehenen
TO-92-Wide-Footprint auf 2.54 mm benachbarten Rasterabstand formen; die E/B/C-
Reihenfolge bleibt unverändert. U1 wird direkt eingelötet; ein zusätzlicher
IC-Sockel ist nicht Teil dieser geprüften Stückliste oder des Höhenmodells.

Für die PCB-Montage sind je Carrier vier **M3×10-Schrauben und vier M3-Muttern
aus PA/Nylon** vorgesehen (für zwei: je acht, Einkauf je zehn). Metallteile
an diesen Positionen sind wegen des Antennenabstands nicht austauschbar.
Die genauen mechanischen Befestigungen und Druckteile führt die Gehäuseanleitung.

J2 hat sechs SMD-Signalkontakte und vier SMD-Schirmanker. Er ist das einzige
feinere SMD-Teil; unter Vergrößerung löten und auf Brücken prüfen oder diese
Position vom Bestückungsdienst montieren lassen. Keine beliebige USB-C-Buchse
mit gleichem Außenmaß einsetzen. Alle übrigen Bauteile sind durchkontaktiert.
